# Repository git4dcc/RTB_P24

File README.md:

# RTB_P24

This simple module is a decoder test board with two [Next18](https://normen.railcommunity.de/RCN-118.pdf) sockets and is part of my growing collection of tools for my DCC based digital model trains. It has two independent Next18 sockets and the DCC signal is fed in and out at both ends to enable easy daisy chaining of multiple PCBs. For each, a motor or resistor can be connected externally to enable service mode programming with DCC.

<details>
<summary>See also</summary>

- [RTB_D21](https://github.com/git4dcc/RTB_D21) (DCC Decoder)
- [RTB_P21](https://github.com/git4dcc/RTB_P21)
- [RTB_P27](https://github.com/git4dcc/RTB_P27)

</details>

<details>
<summary>User Guides</summary>

- User Guide - DE (to be done)
- User Guide - EN (to be done)

</details>

# Hardware
My PCB layout uses SMD footprints with mainly 0603 parts. Reflow soldering is my recommendation, but with some experience handsoldering is also possible.

## PCB
- 2-layer PCB, FR4, 1.6mm
- Dimensions: 80mm x 22mm
- Socket: 2x [Next18](https://normen.railcommunity.de/RCN-118.pdf)

## Kicad
[Schematic](doc/P24_schematic.pdf) | [Layout](doc/P24_layout.pdf) | [Gerber](gerber)

<details>
<summary>Dependency</summary>
<br>

:yellow_circle: Requires my Kicad project library [RTB_SamacSys](https://github.com/git4dcc/RTB_SamacSys) in the same directory tree.

</details>

# Images

This project is intended for hobby use only and is distributed in accordance with the Apache License 2.0 agreement.

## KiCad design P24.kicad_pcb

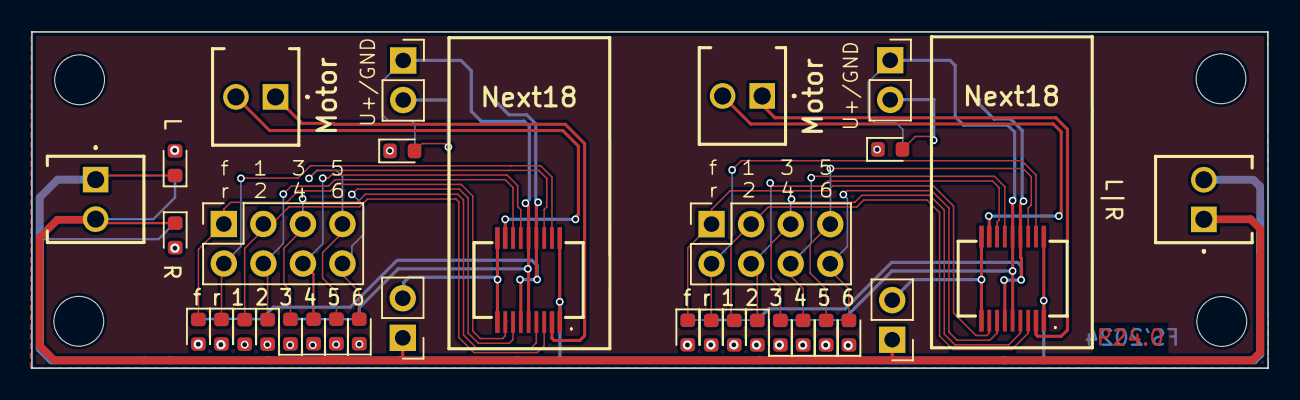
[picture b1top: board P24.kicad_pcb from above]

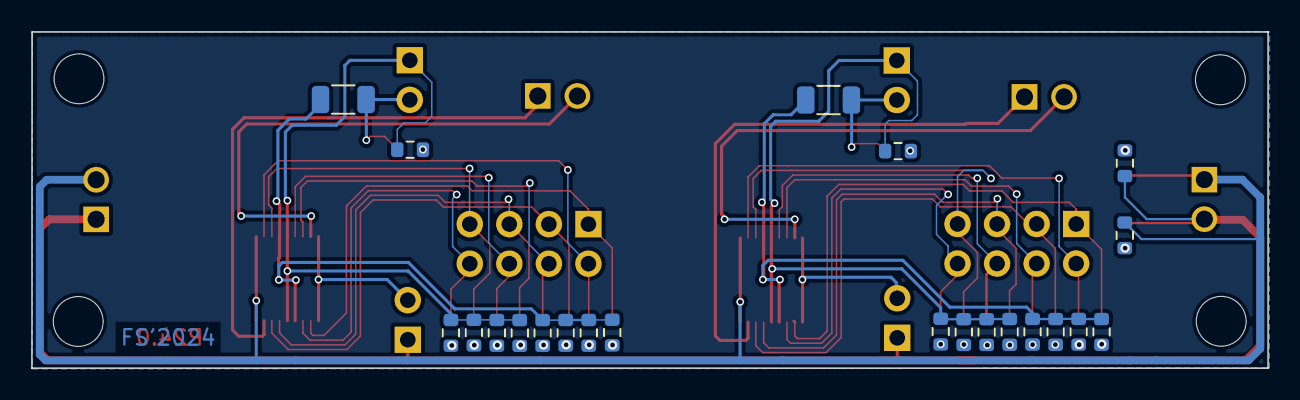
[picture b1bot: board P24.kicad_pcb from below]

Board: 2 copper layers, 79.4 x 21.6 mm, 58 parts (22 on the bottom side), 50 nets.

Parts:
D1, D2, D3, D4, D5, D6, D7, D8, D9, D10, D11, D12, D13, D14, D15, D16, D17, D18, D19, D20: LED_Small_ALT; LED_0603_1608Metric
H1, H2, H3, H4: MountingHole; MountingHole_3.2mm_M3_DIN965
J1, J6: Conn_01x08; PinSocket_2x04_P2.54mm_Vertical
J2, J4: Conn_02x09_Counter_Clockwise; AXK5F16547YG
J3, J7: Conn_01x03_Male; PinSocket_1x02_P2.54mm_Vertical
J5, J8: Conn_01x02; PinHeader_1x02_P2.54mm_Vertical
J9, J10: DCC; 1725656
J11, J12: Conn_01x03_Male; 1725656
R1, R2, R3, R4, R5, R6, R7, R8, R9, R10, R19, R20: 10k; R_0603_1608Metric
R11, R12, R13, R14, R15, R16, R17, R18: 2.2k; R_0603_1608Metric
R21, R22: 22; R_1206_3216Metric

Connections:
Aux1.a: D6.1, J4.3, J6.3
Aux1.b: D4.1, J1.3, J2.3
Aux2.a: D7.1, J4.12, J6.4
Aux2.b: D5.1, J1.4, J2.12
Aux3.a: D16.2, J4.4, J6.5
Aux3.b: D12.2, J1.5, J2.4
Aux4.a: D17.2, J4.13, J6.6
Aux4.b: D13.2, J1.6, J2.13
Aux5.a: D18.2, J4.16, J6.7
Aux5.b: D14.2, J1.7, J2.16
Aux6.a: D19.2, J4.7, J6.8
Aux6.b: D15.2, J1.8, J2.7
F0_f.a: D9.1, J4.8, J6.1
F0_f.b: D3.1, J1.1, J2.8
F0_r.a: D8.1, J4.17, J6.2
F0_r.b: D2.1, J1.2, J2.17
GND.a: J4.5, J4.14, J7.1, R15.2, R16.2, R17.2, R18.2, R20.2
GND.b: J2.5, J2.14, J3.1, R11.2, R12.2, R13.2, R14.2, R19.2
Mot+.a: J4.2, J12.1
Mot+.b: J2.2, J11.1
Mot-.a: J4.11, J12.2
Mot-.b: J2.11, J11.2
unnamed: D1.1, R19.1
unnamed: D1.2, J3.2, R22.2
unnamed: D2.2, R1.1
unnamed: D3.2, R2.1
unnamed: D4.2, R3.1
unnamed: D5.2, R4.1
unnamed: D6.2, R5.1
unnamed: D7.2, R6.1
unnamed: D8.2, R7.1
unnamed: D9.2, R8.1
unnamed: D10.1, J5.1, J8.1, J9.1, J10.2, R10.2
unnamed: D10.2, R9.1
unnamed: D11.1, J2.1, J2.18, J4.1, J4.18, J9.2, J10.1, R9.2
unnamed: D11.2, R10.1
unnamed: D12.1, R11.1
unnamed: D13.1, R12.1
unnamed: D14.1, R13.1
unnamed: D15.1, R14.1
unnamed: D16.1, R15.1
unnamed: D17.1, R16.1
unnamed: D18.1, R17.1
unnamed: D19.1, R18.1
unnamed: D20.1, R20.1
unnamed: D20.2, J7.2, R21.2
unnamed: J2.9, J2.10, J8.2
unnamed: J4.9, J4.10, J5.2
U+.a: J4.6, J4.15, R5.2, R6.2, R7.2, R8.2, R21.1
U+.b: J2.6, J2.15, R1.2, R2.2, R3.2, R4.2, R22.1

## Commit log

2024-10-11 initial
